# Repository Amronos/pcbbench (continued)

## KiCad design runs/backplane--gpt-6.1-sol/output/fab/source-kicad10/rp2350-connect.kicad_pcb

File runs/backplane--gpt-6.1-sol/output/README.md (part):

# RP2350 Connect — revision A

An 85 × 70 mm RP2350A development board designed for PCBWay turnkey PCB fabrication and assembly. All 118 electrical components are fitted, including the connectors and sockets. PCBWay procures every BOM item; there are no customer-supplied parts or DNP options. A protected LiPo battery, microSD card, USB cable, and debugger are external accessories.

Open `boards/rp2350-connect/rp2350-connect.kicad_pro`. Its schematic, board, and local symbol/footprint libraries form the canonical project. `.backplane.json` points to it. Manufacturing outputs are in `fab/`; scripts and intermediate verification files are in `scripts/` and `build/`.

## Hardware

| Function | Implementation |
|---|---|
| Processor | Raspberry Pi RP2350A, QFN-60; **A2 or newer silicon required** |
| Program flash | Winbond W25Q128JVSIQ, 16 MB QSPI |
| Working memory | AP Memory APS6404L-3SQR-SN, 8 MB PSRAM; shared QSPI bus, independent CS on GPIO0 |
| USB | USB-C, USB 2.0 full-speed power/data; two 5.1 kΩ CC resistors, ESD protection, TVS, resettable fuse |
| Battery charging | TI BQ24074, USB/battery power path, nominal 499 mA charge current, pack thermistor input |
| Main rail | TPS63060 buck-boost, regulated 3.3 V from the charger system output |
| Core rail | TPS62823 external 1.101 V buck supply |
| Wireless | ESP32-C3-WROOM-02-N4, 2.4 GHz Wi-Fi and Bluetooth LE, RP2350 UART with RTS/CTS |
| Storage | Hirose microSD slot, SPI1, switched 3.3 V supply |
| I²C | JST SH Qwiic/STEMMA QT connector; 3.3 V, 4.7 kΩ pullups |
| RGB | SK6812MINI; separate 5 V boost and AHCT level buffer |
| Debug/expansion | Installed SWD header, separate ESP UART0 socket, two 12-pin GPIO sockets, reset and boot buttons |
| PCB | Six copper layers, 1.6 mm FR-4, ENIG; all components on top |

## Design decisions and operating requirements

The ESP module provides both required radios without RP2350 RF circuitry. Its PCB antenna overhangs the north edge; keep the antenna area clear of copper, batteries, metal, and enclosure hardware. The final stack is F.Cu signal/GND pour, In1.Cu GND, In2.Cu signal, In3.Cu signal, In4.Cu 3V3, B.Cu signal/GND pour. The extra signal layers make room for the fine-pitch MCU escapes. Minimum copper spacing is 0.10 mm, minimum track width 0.127 mm, and routing vias are 0.45/0.20 mm. Filled and copper-capped vias are required, including vias under solder pads.

The RP2350 uses an external core regulator per the external-supply circuit in the RP2350 datasheet. VREG_FB is grounded and LX is intentionally unconnected. Firmware must set VREG.HIZ and must not attempt to change core voltage through the internal regulator. This also avoids the special polarity requirement of the RP2350 internal-regulator inductor. The core rail is fixed near 1.10 V; qualify any overclocking separately.

The battery connector is **JST PH, three pins: 1 = battery positive, 2 = ground, 3 = 10 kΩ NTC thermistor**. This is not the usual two-pin hobby battery connector. Use a protected single-cell 4.2 V lithium-ion/LiPo pack, at least 1000 mAh and rated for at least 500 mA charging, with an appropriate 10 kΩ NTC. The charger does not replace pack overcurrent/undervoltage protection. Do not connect two cells, LiFePO4, or a pack without its required thermistor. Verify mating-cable polarity before use. Battery voltage is `2 × ADC(GPIO26)`, using the measured ADC reference; the divider draws approximately 21 µA at 4.2 V.

At reset the charger input limit is 100 mA, ESP is held in reset, and microSD power is off. Firmware must enumerate USB and obtain its power budget before enabling the radio/card and increasing the input limit. BQ24074 EN1/EN2: `0/0 = 100 mA`, `1/0 = 500 mA`, `0/1 = resistor-programmed limit`, `1/1 = input suspend`. The resistor limit is approximately 500 mA; it is not USB-C current-advertisement detection. CE is active low: GPIO19 high disables charging. Dynamic power management gives the board load priority over charging. Respect USB suspend and unconfigured-device current limits. Standalone USB charger operation requires a firmware power policy; no USB-PD negotiation is provided. Keep RGB brightness low until the available power is known. External 3V3 loads share this budget; no maximum expansion current is guaranteed without thermal/load qualification.

Initialize SD bus outputs low or as inputs before GPIO1 enables its supply. Avoid driving unpowered card inputs high. Start at standard SD initialization speed, then qualify operation up to 24 MHz. Start QSPI PSRAM conservatively and validate timing before increasing its clock. The PSRAM CS uses GPIO0, which requires board-specific memory initialization rather than a generic Pico board configuration.

## GPIO assignment

| GPIO | Use |
|---|---|
| 0 | PSRAM CS1 |
| 1 | SD power enable; also J6 pin 3 |
| 2 / 3 | I²C SDA / SCL |
| 4 / 5 | RP UART TX / RX to ESP GPIO6 RX / GPIO7 TX |
| 6 / 7 | RP CTS / RTS to ESP GPIO4 RTS / GPIO5 CTS |
| 8 / 9 / 10 / 11 | SD MISO / CS / clock / MOSI |
| 12–15 | Expansion GPIO |
| 16 / 17 | ESP enable / boot strap |
| 18 / 20 | Charger EN1 / EN2 |
| 19 | Charger disable (CE high) |
| 21 / 22 | Charger status / USB power-good, active low |
| 23 | RGB data, GRB at 800 kHz |
| 24 | microSD detect, active low |
| 25 | Expansion GPIO |
| 26 | Battery ADC; also exposed at J7 pin 6 |
| 27–29 | Analog-capable expansion GPIO |

Qwiic J5 pins: GND, 3V3, SDA, SCL. Expansion and debug pin-by-pin definitions are in `fab/connector-pinout.csv` and the schematic. Exposed status/control nets already have board functions: take care when driving them from external hardware. GPIOs are 3.3 V logic.

## Programming and manufacture

The RP2350 ROM supports USB recovery: hold BOOT, press/release RESET, then release BOOT and load a board-specific UF2. SWD is available at J8. ESP UART0 is independently available at J3 for loading the official **ESP32-C3-WROOM-02 ESP-AT** firmware. Its command UART is GPIO6/7/5/4, not the UART0 programming pins. Use a 3.3 V UART adapter, share ground, and power the board through USB/battery rather than connecting an adapter supply. Drive ESP EN high and hold ESP BOOT low during reset to enter download mode; release BOOT afterward. For an empty RP2350, EN can be driven from the programming fixture because the MCU pin is initially high impedance. Match flashing offsets to the exact official firmware archive. Application firmware and radio firmware binaries are not included; this is a hardware design, and PCBWay should leave flash blank unless a subsequently approved binary is supplied.

`fab/PCBWAY-INSTRUCTIONS.md` specifies procurement, stackup, via treatment, assembly, orientation, and first-article checks. `fab/TEST-PLAN.md` describes hardware acceptance and the additional firmware-assisted tests needed to qualify the first article. Gerbers, separate plated/non-plated drill files, BOM, placement CSV, assembly drawings, schematic PDF, electrical netlist, and verification reports are included. The position file includes both SMT and through-hole components. PCBWay must check rotations against the assembly drawing and local footprints rather than assuming a distributor's rotation convention.

## Review status

Verification results are recorded in `fab/verification/` and `fab/RELEASE-STATUS.md`. This revision has not been physically built or measured. Firmware timing, RF performance, USB signal integrity, charger thermistor thresholds, thermal behavior, and battery operation require first-article validation. The schematic nets were independently compared to the frozen component specification. Hardware checks do not establish functional firmware correctness.

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
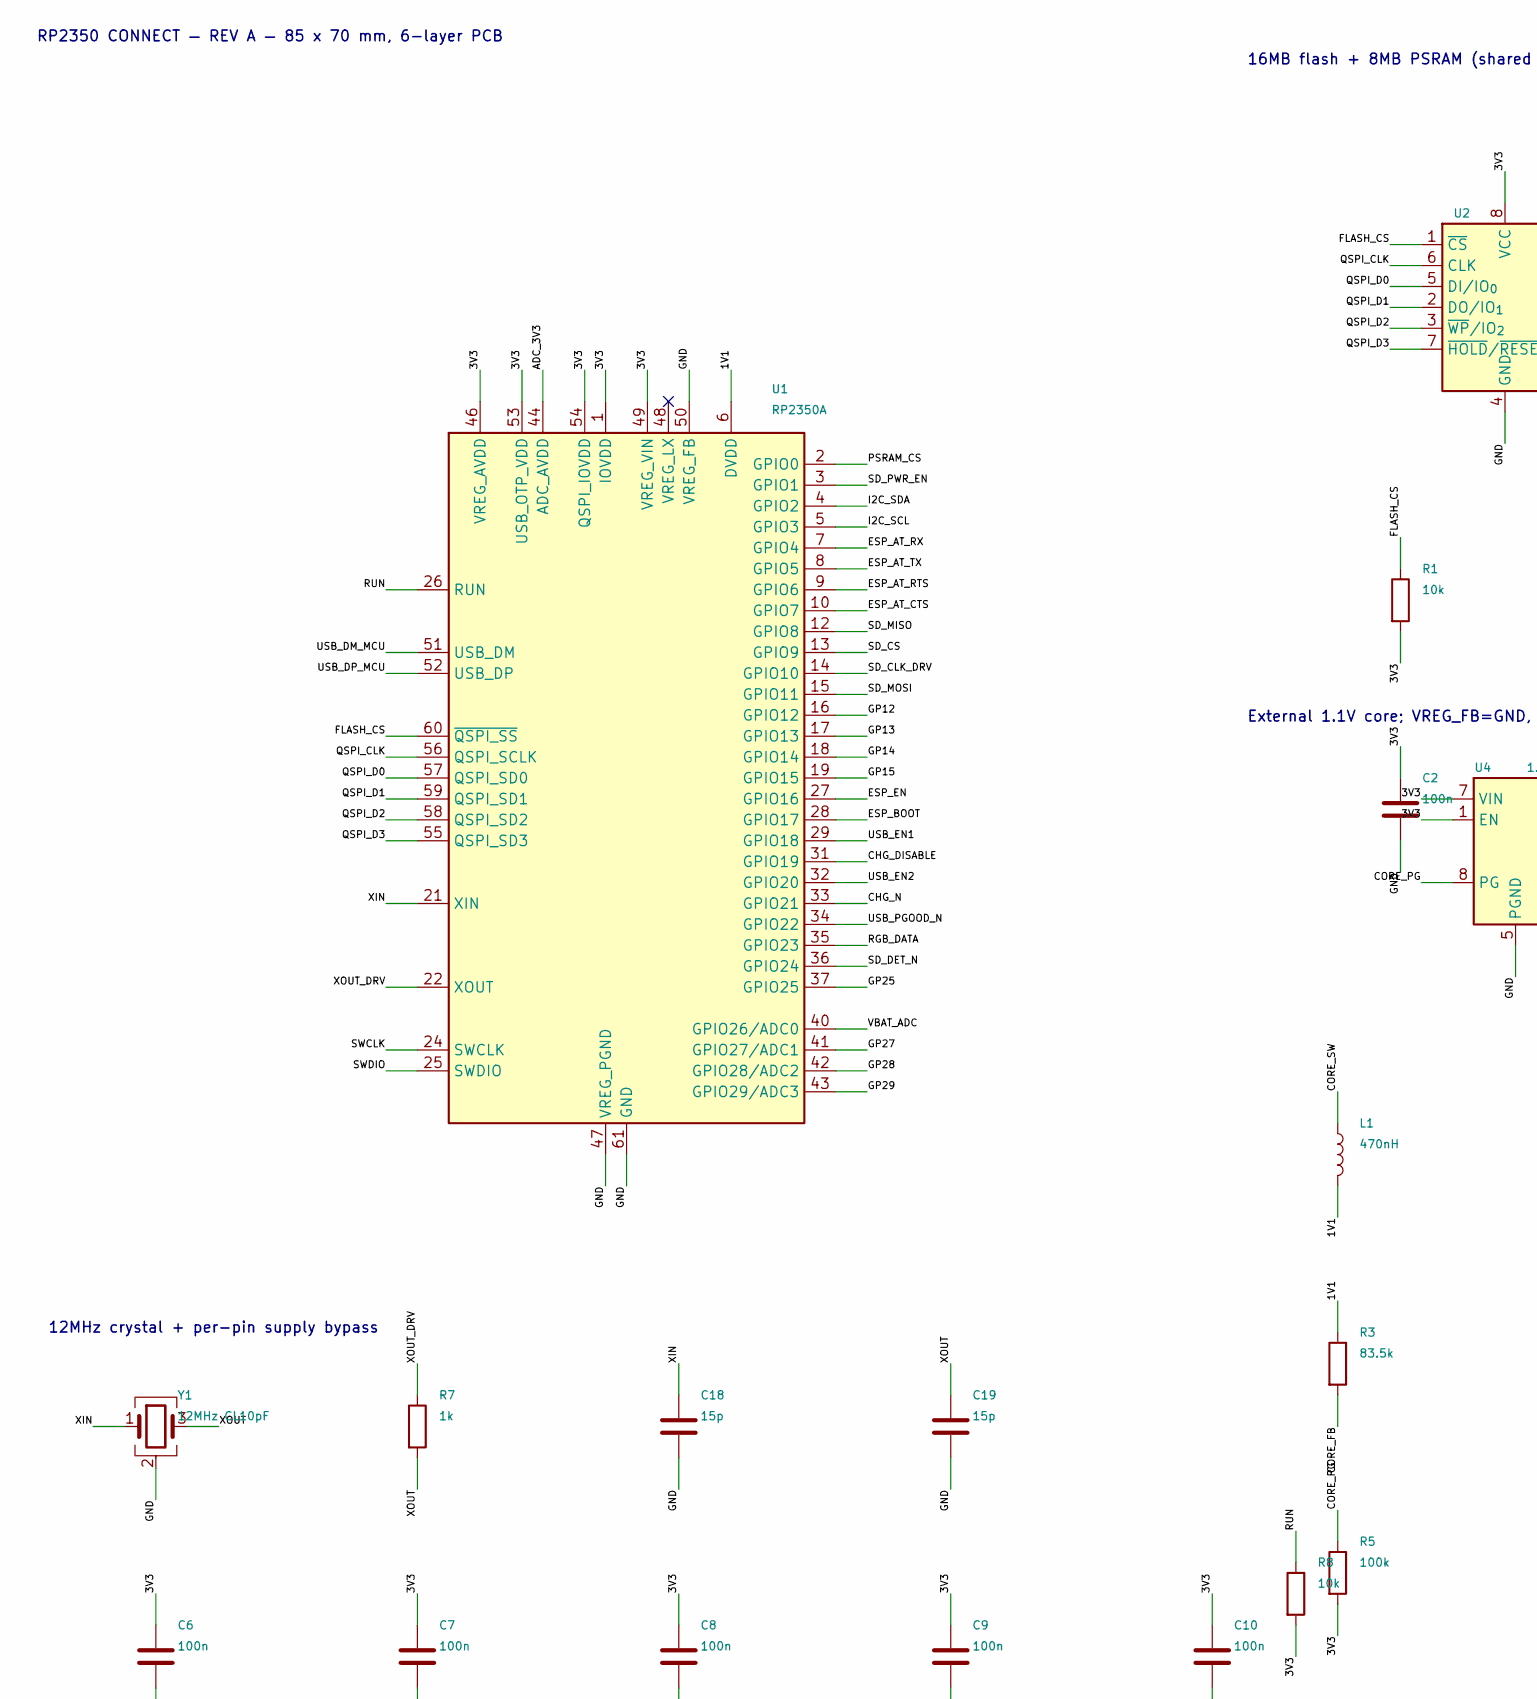
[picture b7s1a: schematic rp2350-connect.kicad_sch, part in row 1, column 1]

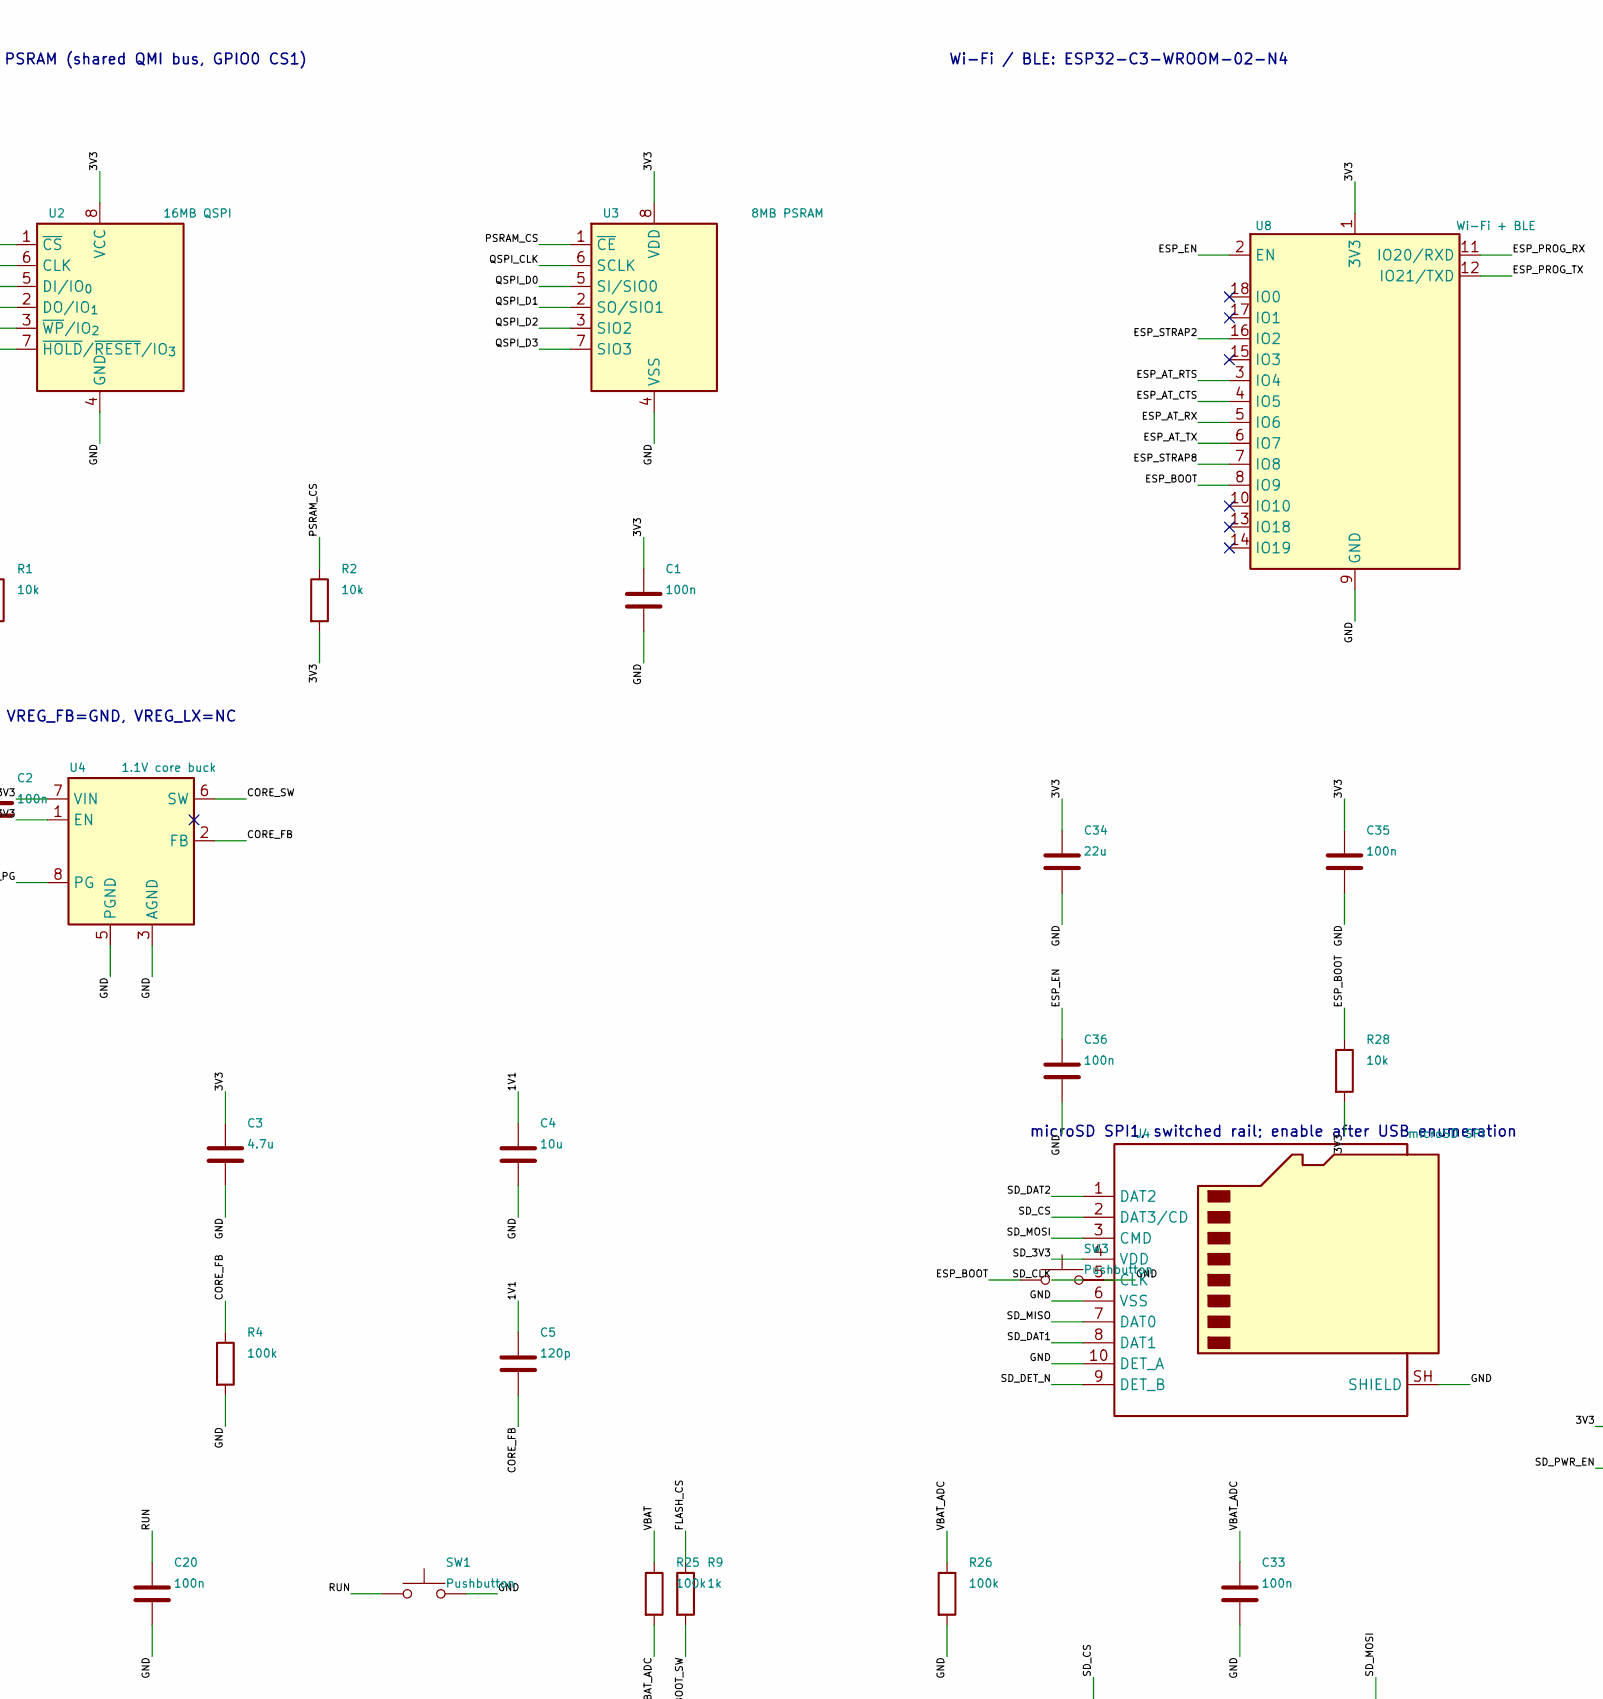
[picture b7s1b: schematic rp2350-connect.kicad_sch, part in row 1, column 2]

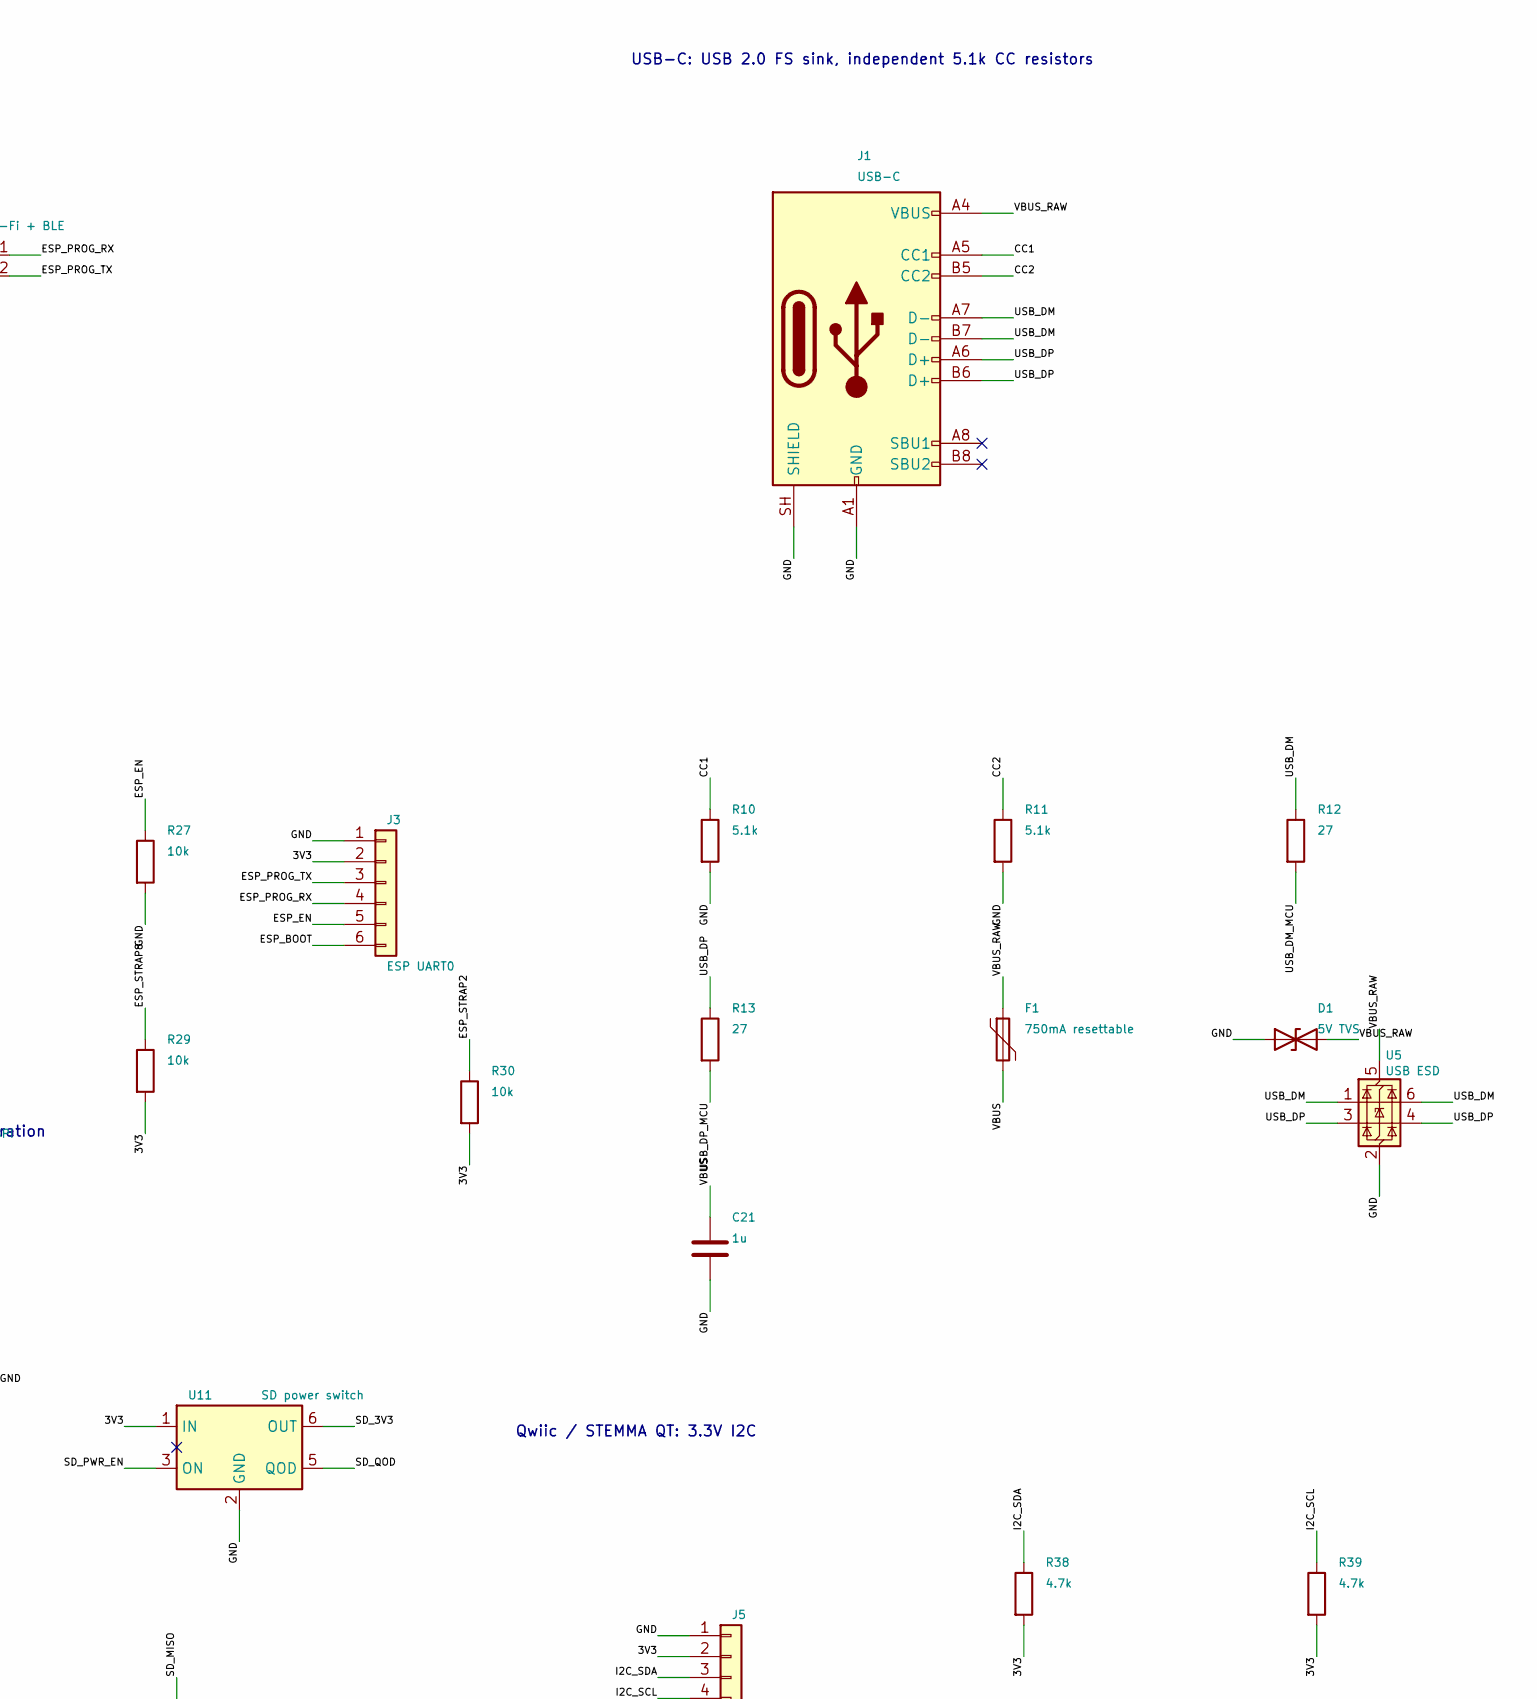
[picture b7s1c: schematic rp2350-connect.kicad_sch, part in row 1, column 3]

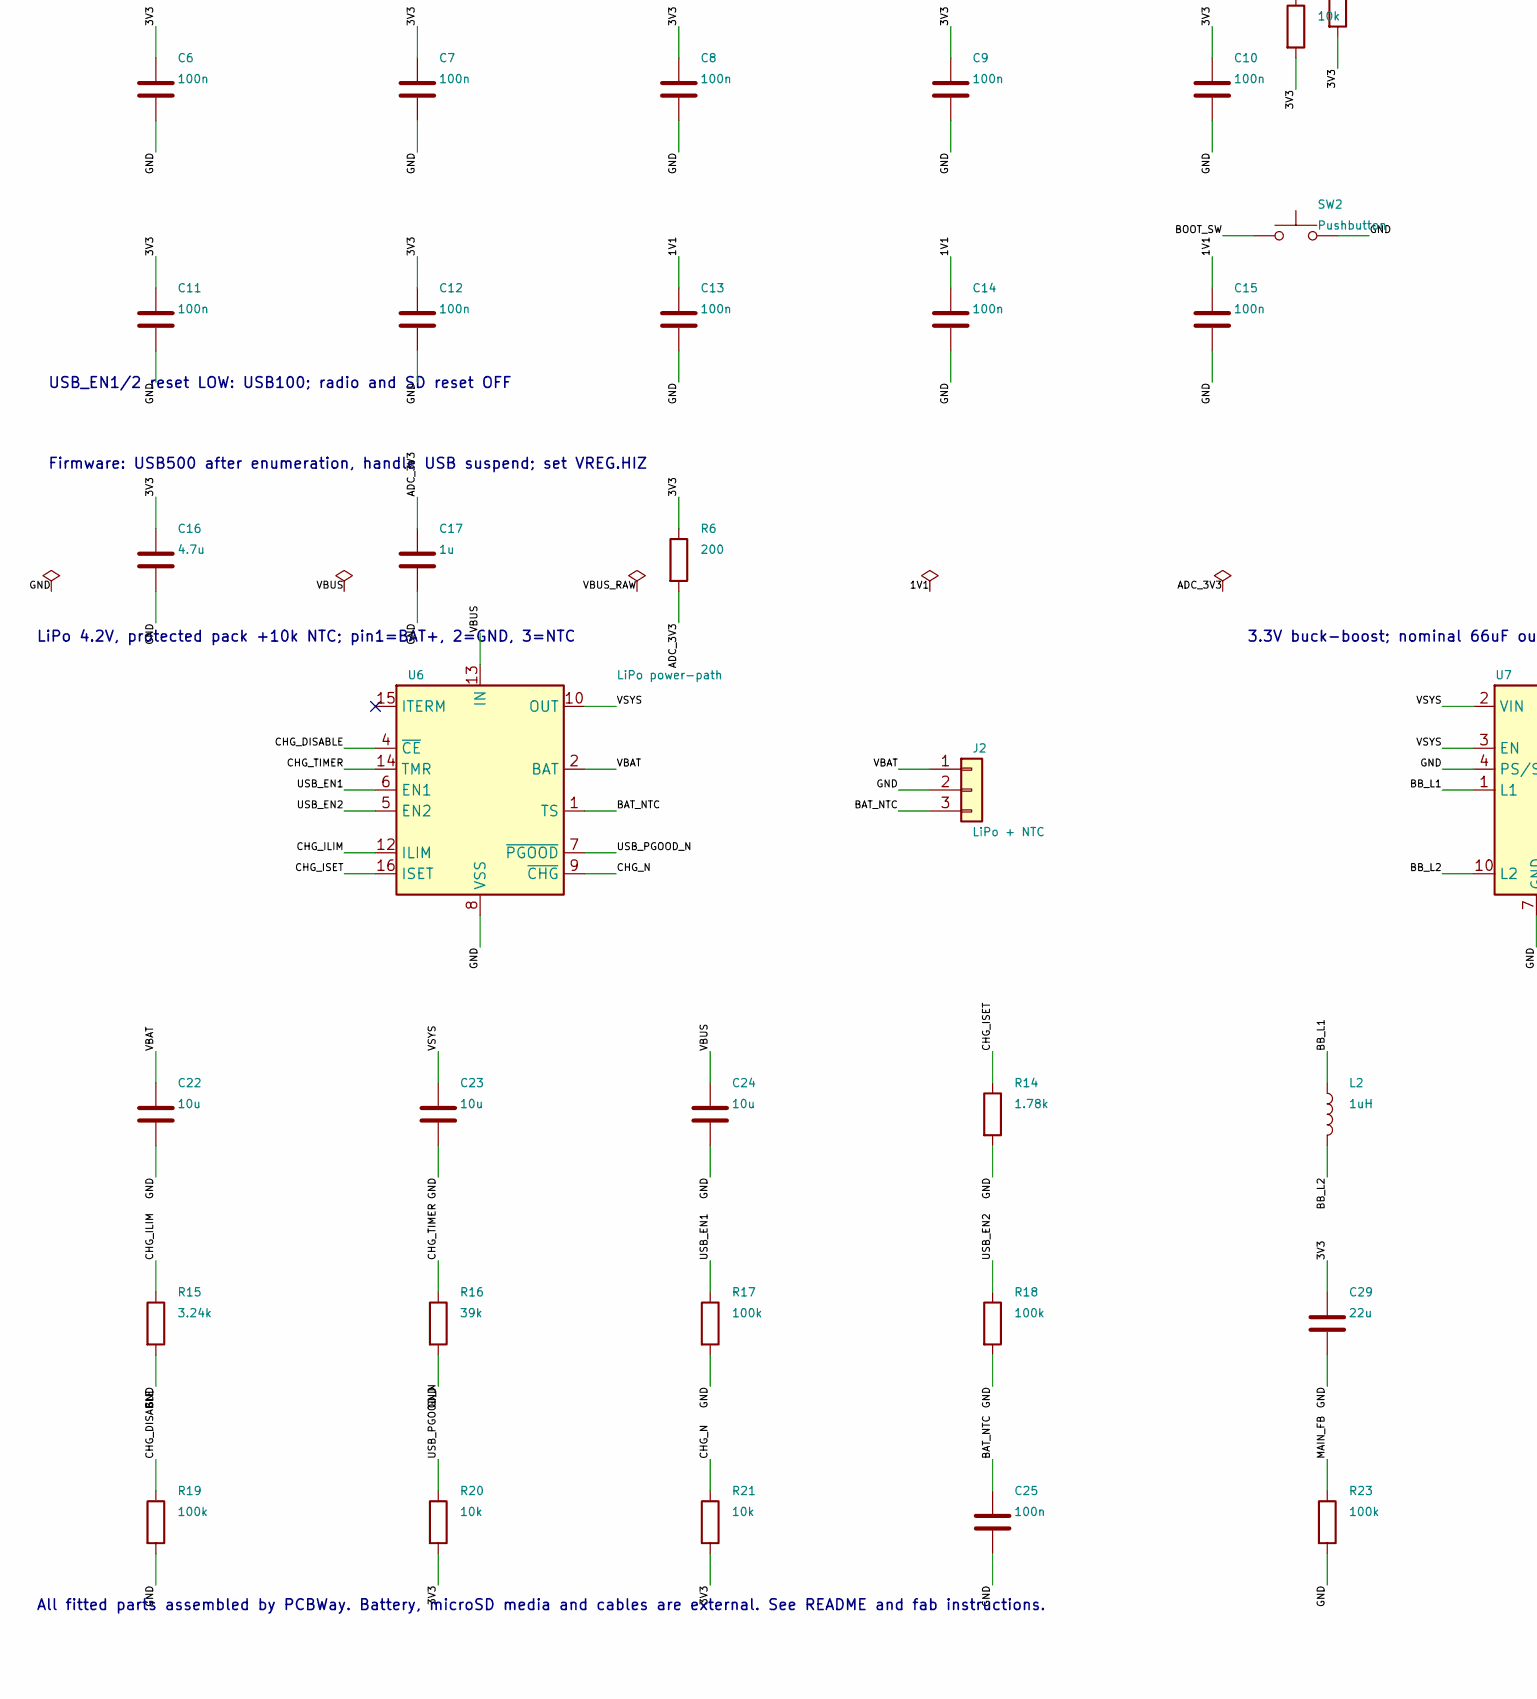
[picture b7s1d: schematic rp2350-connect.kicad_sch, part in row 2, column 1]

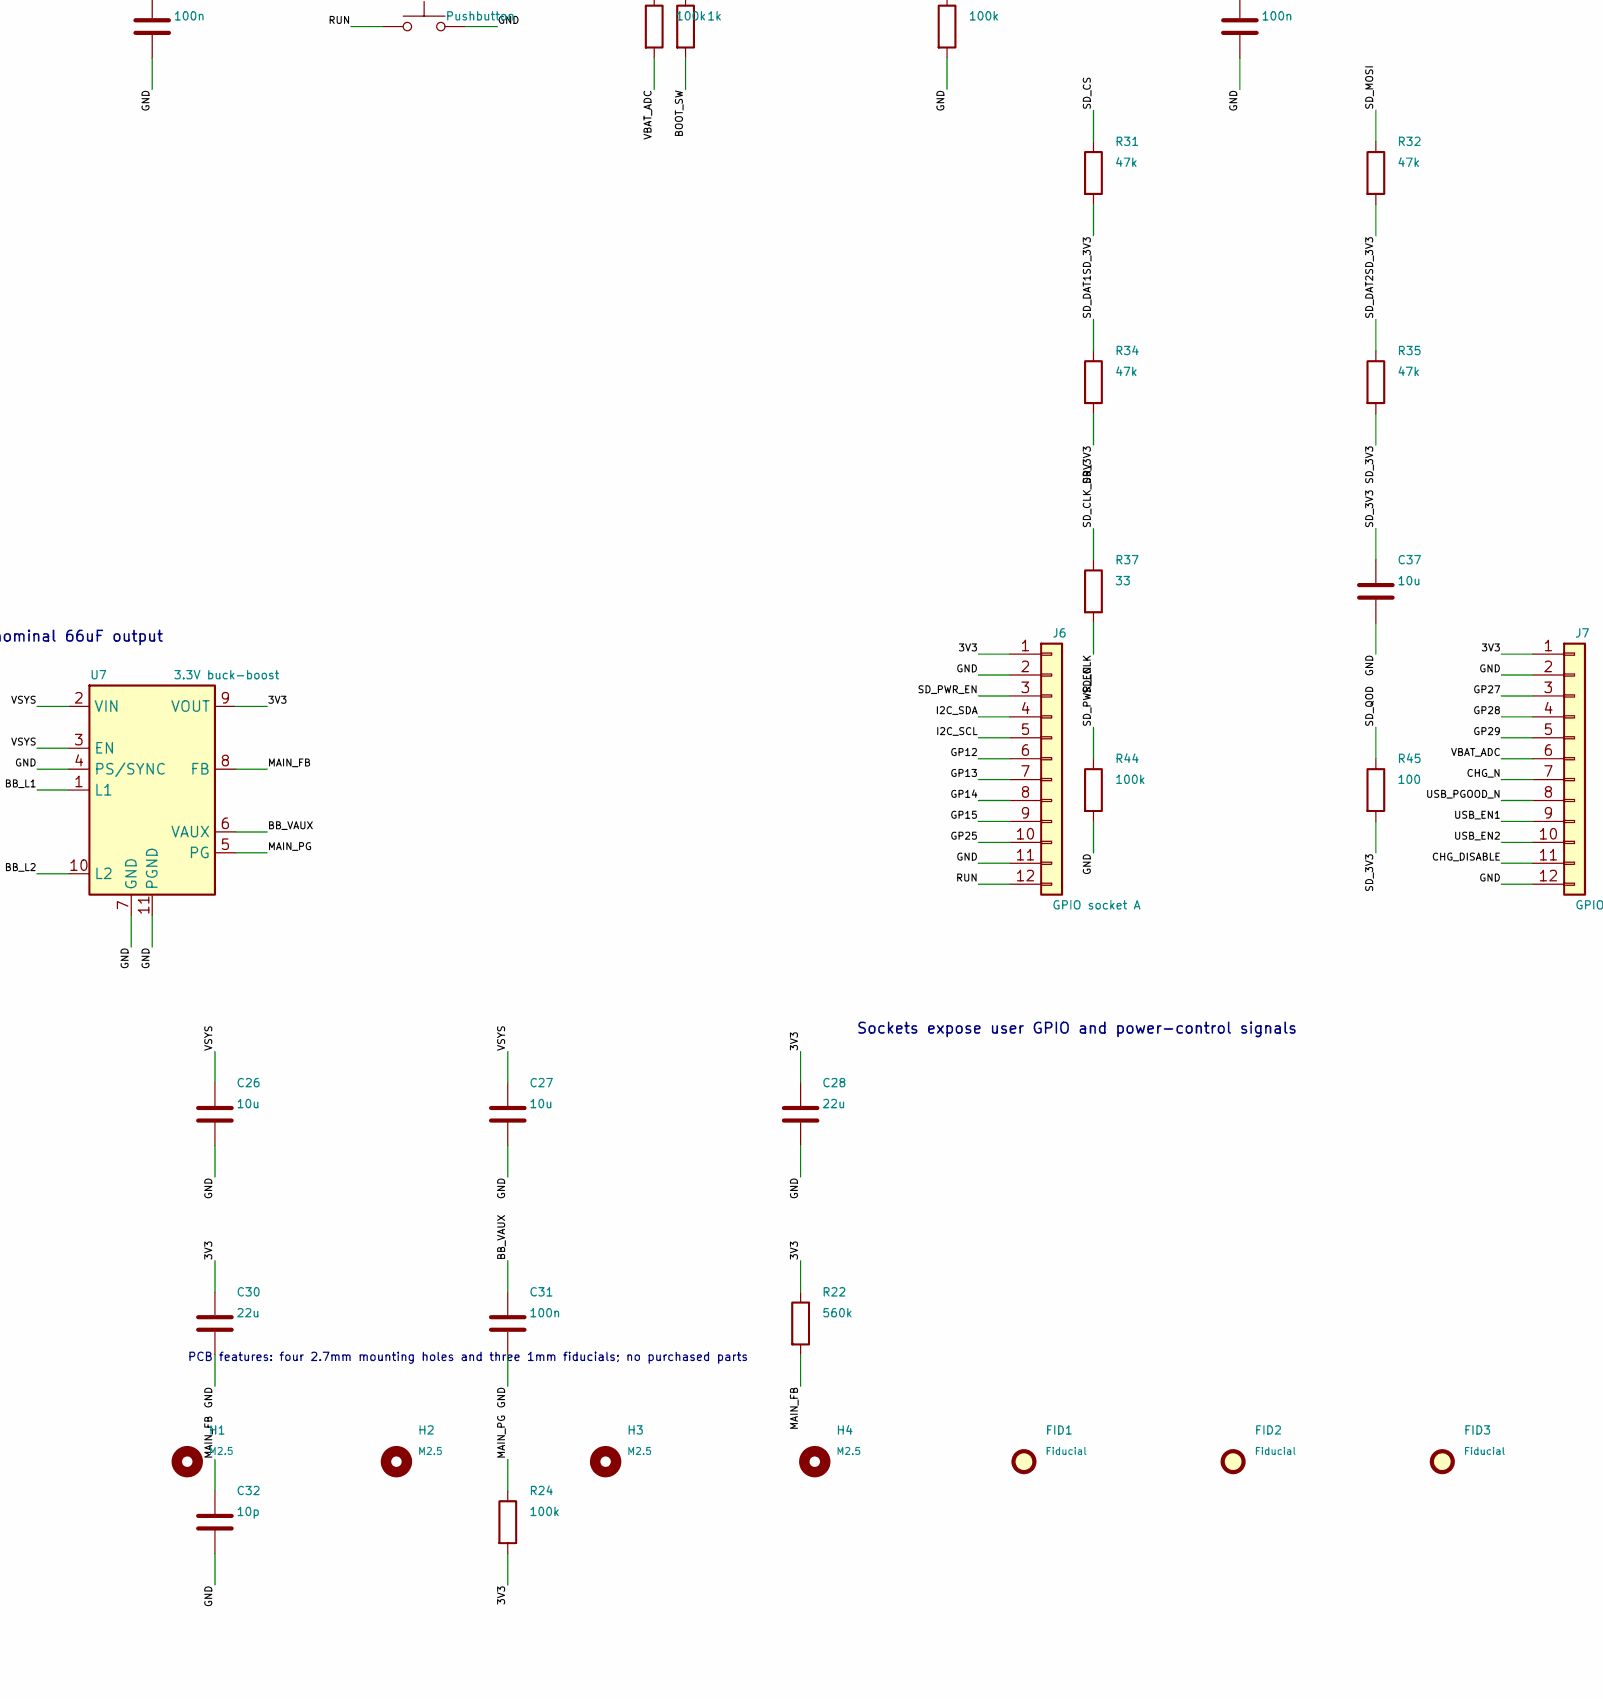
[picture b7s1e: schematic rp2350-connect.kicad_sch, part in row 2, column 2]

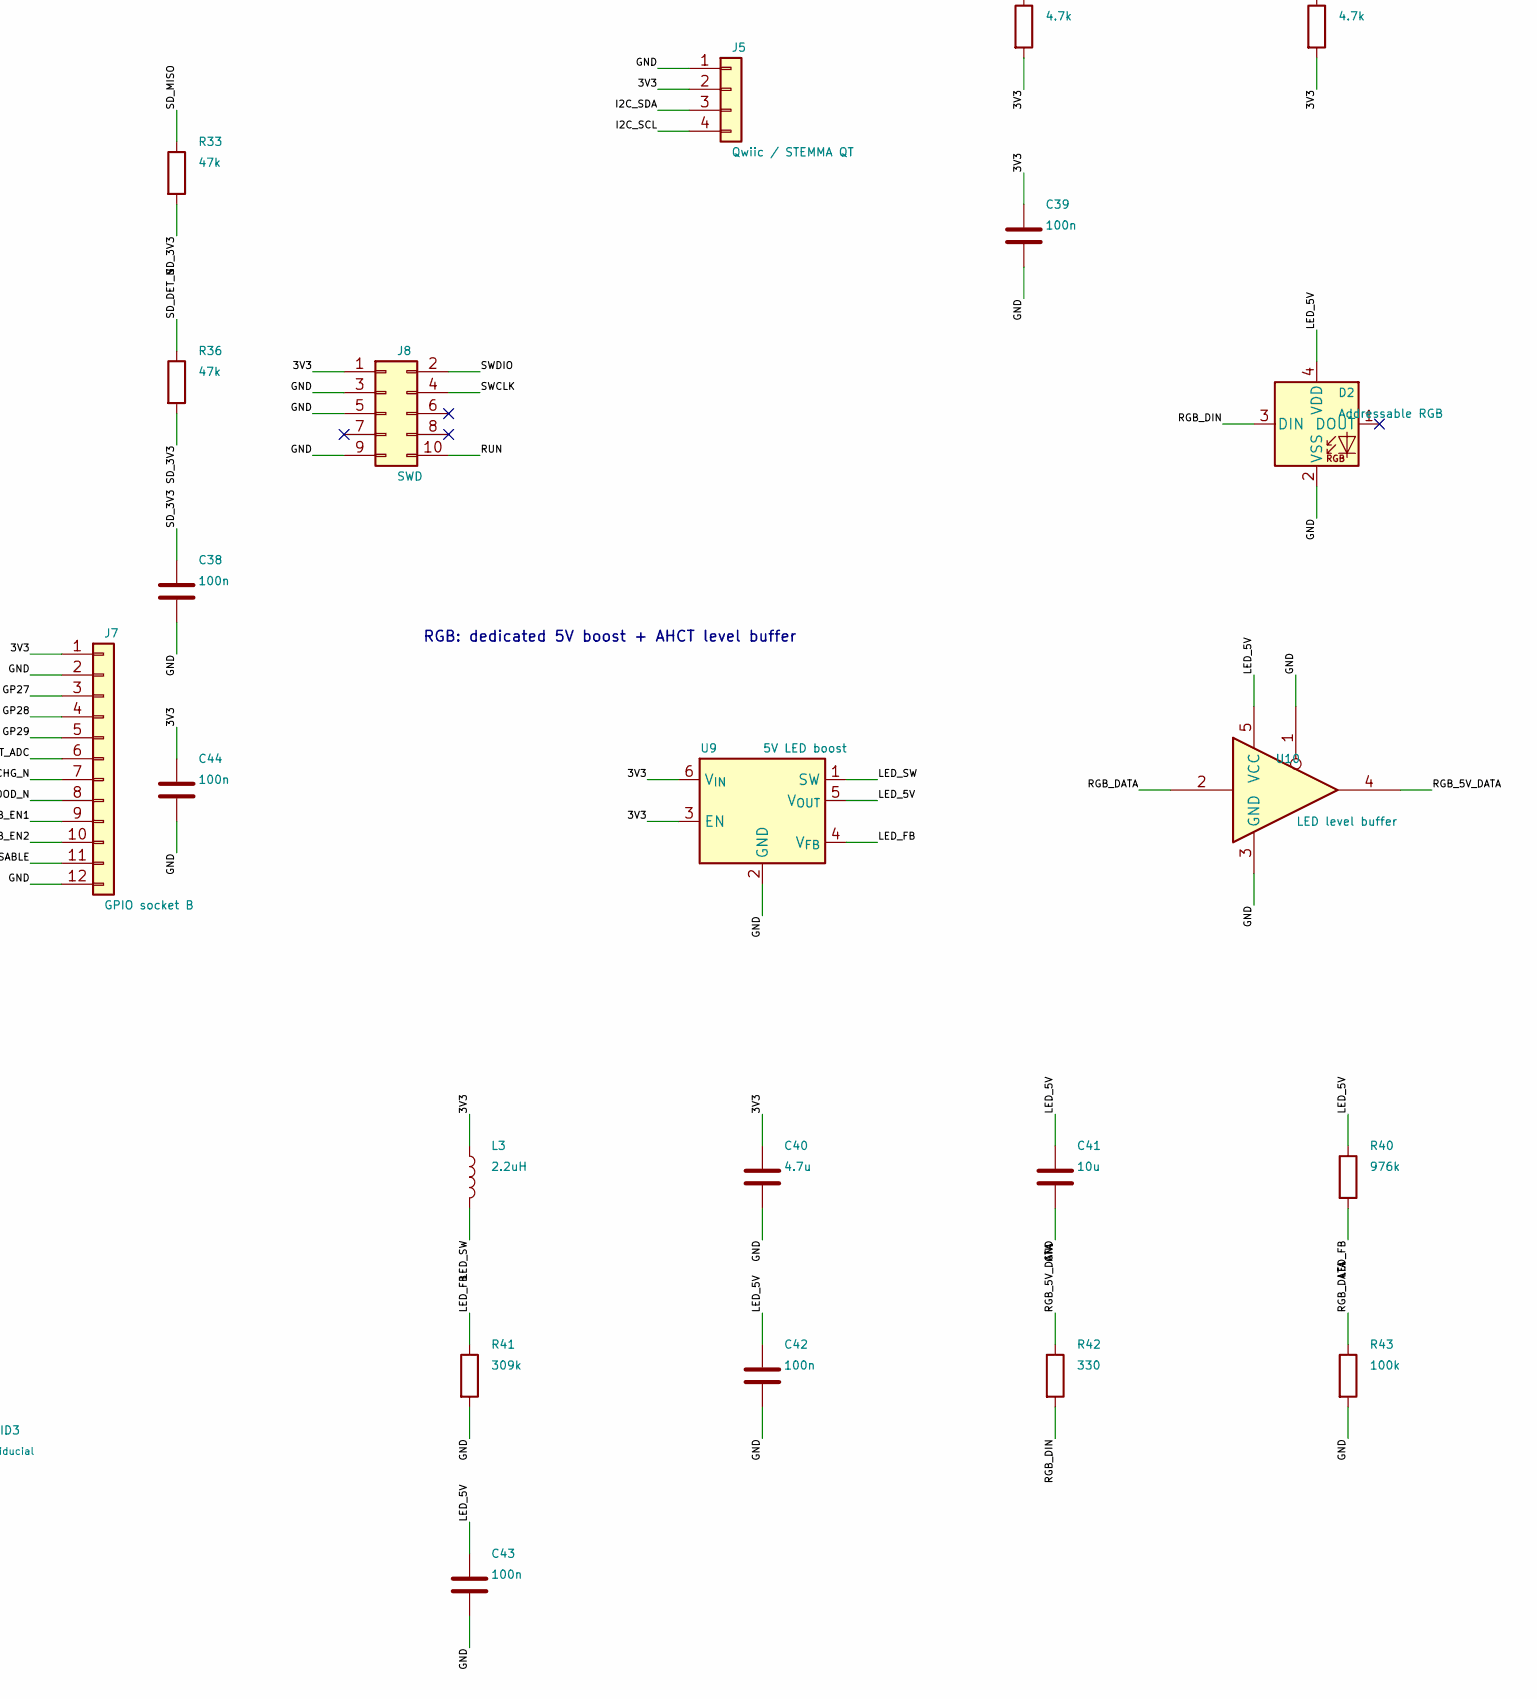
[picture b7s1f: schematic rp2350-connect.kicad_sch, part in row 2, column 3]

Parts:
C1, C2, C20, C25, C31, C33, C35, C36, C38, C39, C42, C43, C44: 100n; C_0603_1608Metric; MPN GRM188R71C104KA01D
C3, C16, C40: 4.7u; C_0805_2012Metric; MPN GRM21BR61A475KA73L
C4, C22, C23, C24, C26, C27, C37, C41: 10u; C_0805_2012Metric; MPN GRM21BR61A106KE19L
C5: 120p; C_0603_1608Metric; MPN GRM1885C1H121JA01D
C6, C7, C8, C9, C10, C11, C12, C13, C14, C15: 100n; C_0402_1005Metric; MPN GRM155R71C104KA88D
C17, C21: 1u; C_0603_1608Metric; MPN GRM188R61C105KA93D
C18, C19: 15p; C_0402_1005Metric; MPN GRM1555C1H150JA01D
C28, C29, C30, C34: 22u; C_1206_3216Metric; MPN GRM31CR61A226KE19L
C32: 10p; C_0603_1608Metric; MPN GRM1885C1H100JA01D
D1: 5V TVS; D_SOD-123F; MPN SMF5.0A
D2: Addressable RGB; LED_SK6812MINI_PLCC4_3.5x3.5mm_P1.75mm; MPN SK6812MINI
F1: 750mA resettable; Fuse_1812_4532Metric; MPN MF-MSMF075-2
FID1, FID2, FID3: Fiducial; Fiducial_1mm_Mask2mm
H1, H2, H3, H4: M2.5; MountingHole_2.7mm_M2.5
J1: USB-C; USB_C_Receptacle_GCT_USB4105-xx-A_16P_TopMnt_Horizontal; MPN USB4105-GF-A
J2: LiPo + NTC; JST_PH_B3B-PH-K_1x03_P2.00mm_Vertical; MPN B3B-PH-K-S(LF)(SN)
J3: ESP UART0; PinSocket_1x06_P2.54mm_Vertical; MPN SSQ-106-03-G-S
J4: microSD SPI; microSD_HC_Hirose_DM3AT-SF-PEJM5; MPN DM3AT-SF-PEJM5
J5: Qwiic / STEMMA QT; JST_SH_SM04B-SRSS-TB_1x04-1MP_P1.00mm_Horizontal; MPN SM04B-SRSS-TB(LF)(SN)
J6: GPIO socket A; PinSocket_1x12_P2.54mm_Vertical; MPN SSQ-112-03-G-S
J7: GPIO socket B; PinSocket_1x12_P2.54mm_Vertical; MPN SSQ-112-03-G-S
J8: SWD; PinHeader_2x05_P1.27mm_Vertical; MPN FTSH-105-01-L-D-K
L1: 470nH; L_Murata_DFE201610P; MPN DFE201610P-R47M=P2
L2: 1uH; L_Murata_DFE201610P; MPN DFE201610P-1R0M=P2
L3: 2.2uH; L_Murata_DFE201610P; MPN DFE201610P-2R2M=P2
R1, R2, R8, R20, R21, R27, R28, R29, R30: 10k; R_0603_1608Metric; MPN RC0603FR-0710KL
R3: 83.5k; R_0603_1608Metric; MPN RC0603FR-0783K5L
R4, R5, R17, R18, R19, R23, R24, R25, R26, R43, R44: 100k; R_0603_1608Metric; MPN RC0603FR-07100KL
R6: 200; R_0603_1608Metric; MPN RC0603FR-07200RL
R7, R9: 1k; R_0603_1608Metric; MPN RC0603FR-071KL
R10, R11: 5.1k; R_0603_1608Metric; MPN RC0603FR-075K1L
R12, R13: 27; R_0603_1608Metric; MPN RC0603FR-0727RL
R14: 1.78k; R_0603_1608Metric; MPN RC0603FR-071K78L
R15: 3.24k; R_0603_1608Metric; MPN RC0603FR-073K24L
R16: 39k; R_0603_1608Metric; MPN RC0603FR-0739KL
R22: 560k; R_0603_1608Metric; MPN RC0603FR-07560KL
R31, R32, R33, R34, R35, R36: 47k; R_0603_1608Metric; MPN RC0603FR-0747KL
R37: 33; R_0603_1608Metric; MPN RC0603FR-0733RL
R38, R39: 4.7k; R_0603_1608Metric; MPN RC0603FR-074K7L
R40: 976k; R_0603_1608Metric; MPN RC0603FR-07976KL
R41: 309k; R_0603_1608Metric; MPN RC0603FR-07309KL
R42: 330; R_0603_1608Metric; MPN RC0603FR-07330RL
R45: 100; R_0603_1608Metric; MPN RC0603FR-07100RL
SW1, SW2, SW3: Pushbutton; SW_SPST_PTS810; MPN PTS810SJM250SMTRLFS
U1: RP2350A; QFN-60-1EP_7x7mm_P0.4mm_EP3.4x3.4mm; MPN RP2350A
U2: 16MB QSPI; SOIC-8_5.3x5.3mm_P1.27mm; MPN W25Q128JVSIQ
U3: 8MB PSRAM; SOIC-8_3.9x4.9mm_P1.27mm; MPN APS6404L-3SQR-SN
U4: 1.1V core buck; Texas_VSON-HR-8_1.5x2mm_P0.5mm; MPN TPS62823DLCR
U5: USB ESD; SOT-23-6; MPN USBLC6-2SC6
U6: LiPo power-path; VQFN-16-1EP_3x3mm_P0.5mm_EP1.6x1.6mm; MPN BQ24074RGTR
U7: 3.3V buck-boost; Texas_S-PWSON-N10; MPN TPS63060DSCR
U8: Wi-Fi + BLE; ESP32-C3-WROOM-02; MPN ESP32-C3-WROOM-02-N4
U9: 5V LED boost; SOT-23-6_LED; MPN MCP1640T-I/CHY
U10: LED level buffer; SOT-23-5; MPN SN74AHCT1G125DBVR
U11: SD power switch; SOT-363_SC-70-6; MPN TPS22919DCKR
Y1: 12MHz CL10pF; Crystal_SMD_3225-4Pin_3.2x2.5mm; MPN ABM8-272-T3

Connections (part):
/1V1: C4.1, C5.1, C13.1, C14.1, C15.1, L1.2, R3.1, U1.6 (DVDD), U1.23 (DVDD), U1.39 (DVDD)
/3V3: C1.1, C2.1, C3.1, C6.1, C7.1, C8.1, C9.1, C10.1, C11.1, C12.1, C16.1, C28.1, C29.1, C30.1, C34.1, C35.1, C39.1, C40.1, C44.1, J3.2, J5.2, J6.1, J7.1, J8.1, L3.1, R1.2, R2.2, R5.2, R6.1, R8.2, R20.2, R21.2, R22.1, R24.2, R28.2, R29.2, R30.2, R38.2, R39.2, U1.1 (IOVDD), U1.11 (IOVDD), U1.20 (IOVDD), U1.30 (IOVDD), U1.38 (IOVDD), U1.45 (IOVDD), U1.46 (VREG_AVDD), U1.49 (VREG_VIN), U1.53 (USB_OTP_VDD), U1.54 (QSPI_IOVDD), U2.8 (VCC), U3.8 (VDD), U4.1 (EN), U4.7 (VIN), U7.9 (VOUT), U8.1 (3V3), U9.3 (EN), U9.6 (V_{IN}), U11.1 (IN)
/ADC_3V3: C17.1, R6.2, U1.44 (ADC_AVDD)
/BAT_NTC: C25.1, J2.3, U6.1 (TS)
/BB_L1: L2.1, U7.1 (L1)
/BB_L2: L2.2, U7.10 (L2)
/BB_VAUX: C31.1, U7.6 (VAUX)
/BOOT_SW: R9.2, SW2.1
/CC1: J1.A5 (CC1), R10.1
/CC2: J1.B5 (CC2), R11.1
/CHG_DISABLE: J7.11, R19.1, U1.31 (GPIO19), U6.4 (~CE)
/CHG_ILIM: R15.1, U6.12 (ILIM)
/CHG_ISET: R14.1, U6.16 (ISET)
/CHG_N: J7.7, R21.1, U1.33 (GPIO21), U6.9 (~CHG)
/CHG_TIMER: R16.1, U6.14 (TMR)
/CORE_FB: C5.2, R3.2, R4.1, U4.2 (FB)
/CORE_PG: R5.1, U4.8 (PG)
/CORE_SW: L1.1, U4.6 (SW)
/ESP_AT_CTS: U1.10 (GPIO7), U8.4 (IO5)
/ESP_AT_RTS: U1.9 (GPIO6), U8.3 (IO4)
/ESP_AT_RX: U1.7 (GPIO4), U8.5 (IO6)
/ESP_AT_TX: U1.8 (GPIO5), U8.6 (IO7)
/ESP_BOOT: J3.6, R28.1, SW3.1, U1.28 (GPIO17), U8.8 (IO9)
/ESP_EN: C36.1, J3.5, R27.1, U1.27 (GPIO16), U8.2 (EN)
/ESP_PROG_RX: J3.4, U8.11 (IO20/RXD)
/ESP_PROG_TX: J3.3, U8.12 (IO21/TXD)
/ESP_STRAP2: R30.1, U8.16 (IO2)
/ESP_STRAP8: R29.1, U8.7 (IO8)
/FLASH_CS: R1.1, R9.1, U1.60 (~QSPI_SS), U2.1 (~CS)
/GND: C1.2, C2.2, C3.2, C4.2, C6.2, C7.2, C8.2, C9.2, C10.2, C11.2, C12.2, C13.2, C14.2, C15.2, C16.2, C17.2, C18.2, C19.2, C20.2, C21.2, C22.2, C23.2, C24.2, C25.2, C26.2, C27.2, C28.2, C29.2, C30.2, C31.2, C32.2, C33.2, C34.2, C35.2, C36.2, C37.2, C38.2, C39.2, C40.2, C41.2, C42.2, C43.2, C44.2, D1.1 (A1), D2.2 (VSS), J1.A1 (GND), J1.A12 (GND), J1.B1 (GND), J1.B12 (GND), J1.SH (SHIELD), J2.2, J3.1, J4.6 (VSS), J4.10 (DET_A), J4.SH (SHIELD), J5.1, J6.2, J6.11, J7.2, J7.12, J8.3, J8.5, J8.9, R4.2, R10.2, R11.2, R14.2, R15.2, R16.2, R17.2, R18.2, R19.2, R23.2, R26.2, R27.2, R41.2, R43.2, R44.2, SW1.2, SW2.2, SW3.2, U1.47 (VREG_PGND), U1.50 (VREG_FB), U1.61 (GND), U2.4 (GND)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
/GP12: J6.6, U1.16 (GPIO12)
/GP13: J6.7, U1.17 (GPIO13)
/GP14: J6.8, U1.18 (GPIO14)
/GP15: J6.9, U1.19 (GPIO15)
/GP25: J6.10, U1.37 (GPIO25)
/GP27: J7.3, U1.41 (GPIO27/ADC1)
/GP28: J7.4, U1.42 (GPIO28/ADC2)
/GP29: J7.5, U1.43 (GPIO29/ADC3)
/I2C_SCL: J5.4, J6.5, R39.1, U1.5 (GPIO3)
/I2C_SDA: J5.3, J6.4, R38.1, U1.4 (GPIO2)
/LED_5V: C41.1, C42.1, C43.1, D2.4 (VDD), R40.1, U9.5 (V_{OUT}), U10.5 (VCC)
/LED_FB: R40.2, R41.1, U9.4 (V_{FB})
/LED_SW: L3.2, U9.1 (SW)
/MAIN_FB: C32.1, R22.2, R23.1, U7.8 (FB)
/MAIN_PG: R24.1, U7.5 (PG)
/PSRAM_CS: R2.1, U1.2 (GPIO0), U3.1 (~CE)
/QSPI_CLK: U1.56 (QSPI_SCLK), U2.6 (CLK), U3.6 (SCLK)
/QSPI_D0: U1.57 (QSPI_SD0), U2.5 (DI/IO_{0}), U3.5 (SI/SIO0)
/QSPI_D1: U1.59 (QSPI_SD1), U2.2 (DO/IO_{1}), U3.2 (SO/SIO1)
/QSPI_D2: U1.58 (QSPI_SD2), U2.3 (~WP/IO_{2}), U3.3 (SIO2)
/QSPI_D3: U1.55 (QSPI_SD3), U2.7 (~HOLD/~RESET/IO_{3}), U3.7 (SIO3)
/RGB_5V_DATA: R42.1, U10.4
/RGB_DATA: R43.1, U1.35 (GPIO23), U10.2
/RGB_DIN: D2.3 (DIN), R42.2
/RUN: C20.1, J6.12, J8.10, R8.1, SW1.1, U1.26 (RUN)
/SD_3V3: C37.1, C38.1, J4.4 (VDD), R31.2, R32.2, R33.2, R34.2, R35.2, R36.2, R45.2, U11.6 (OUT)
/SD_CLK: J4.5 (CLK), R37.2
/SD_CLK_DRV: R37.1, U1.14 (GPIO10)
/SD_CS: J4.2 (DAT3/CD), R31.1, U1.13 (GPIO9)
/SD_DAT1: J4.8 (DAT1), R34.1
/SD_DAT2: J4.1 (DAT2), R35.1
/SD_DET_N: J4.9 (DET_B), R36.1, U1.36 (GPIO24)
/SD_MISO: J4.7 (DAT0), R33.1, U1.12 (GPIO8)
/SD_MOSI: J4.3 (CMD), R32.1, U1.15 (GPIO11)
/SD_PWR_EN: J6.3, R44.1, U1.3 (GPIO1), U11.3 (ON)
/SD_QOD: R45.1, U11.5 (QOD)
/SWCLK: J8.4, U1.24 (SWCLK)
/SWDIO: J8.2, U1.25 (SWDIO)
/USB_DM: J1.A7 (D-), J1.B7 (D-), R12.1, U5.1 (I/O1), U5.6 (I/O1)
/USB_DM_MCU: R12.2, U1.51 (USB_DM)
/USB_DP: J1.A6 (D+), J1.B6 (D+), R13.1, U5.3 (I/O2), U5.4 (I/O2)
/USB_DP_MCU: R13.2, U1.52 (USB_DP)
/USB_EN1: J7.9, R17.1, U1.29 (GPIO18), U6.6 (EN1)
/USB_EN2: J7.10, R18.1, U1.32 (GPIO20), U6.5 (EN2)
/USB_PGOOD_N: J7.8, R20.1, U1.34 (GPIO22), U6.7 (~PGOOD)
/VBAT: C22.1, J2.1, R25.1, U6.2 (BAT), U6.3 (BAT)
/VBAT_ADC: C33.1, J7.6, R25.2, R26.1, U1.40 (GPIO26/ADC0)
/VBUS: C21.1, C24.1, F1.2, U6.13 (IN)
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
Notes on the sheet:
3.3V buck-boost; nominal 66uF output
Wi-Fi / BLE: ESP32-C3-WROOM-02-N4
microSD SPI1, switched rail; enable after USB enumeration
All fitted parts assembled by PCBWay. Battery, microSD media and cables are external. See README and fab instructions.
LiPo 4.2V, protected pack +10k NTC; pin1=BAT+, 2=GND, 3=NTC
16MB flash + 8MB PSRAM (shared QMI bus, GPIO0 CS1)
USB-C: USB 2.0 FS sink, independent 5.1k CC resistors
Firmware: USB500 after enumeration, handle USB suspend; set VREG.HIZ
RGB: dedicated 5V boost + AHCT level buffer
Sockets expose user GPIO and power-control signals
12MHz crystal + per-pin supply bypass
External 1.1V core; VREG_FB=GND, VREG_LX=NC
RP2350 CONNECT — REV A — 85 x 70 mm, 6-layer PCB
PCB features: four 2.7mm mounting holes and three 1mm fiducials; no purchased parts
USB_EN1/2 reset LOW: USB100; radio and SD reset OFF
Qwiic / STEMMA QT: 3.3V I2C
